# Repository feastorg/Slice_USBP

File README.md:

<div align="center">
  <!-- Title: -->
  
  <h2><a href="https://github.com/uwo-fast/Slice_TEMP"> STEP Slice </a></h2>
  <!-- Labels: -->
  <!-- First row: -->

  <a href="https://certification.oshwa.org/">
    
    <!-- img src="https://img.shields.io/badge/OSHWA-Certified-darkgreen?style=flat-square" height="20" alt="OSHWA" -->       <!-- img src="https://img.shields.io/badge/OSHWA-Pending-darkorange?style=flat-square" height="20" alt="OSHWA" -->
  </a>

  <!-- Second row: -->
  <br>

  <!-- Short description: -->
  <h3>Universal Serial Bus (USB) Port Slice for BREAD.</h3>
</div>

## Introduction
[Provide a brief introduction to the project, including the motivation and goals. Explain the significance and context of the research.]

## Project Overview
[Describe the project in more detail. This section can be split into subsections if necessary.]

## Installation
[Provide instructions for installing any necessary software or hardware components.]

## Usage
[Explain how to use the project. Include examples and screenshots if applicable.]

### Basic Usage
[Provide basic usage instructions.]

### Advanced Usage
[Provide advanced usage instructions, including any optional features or configurations.]

## Documentation
[Link to the detailed documentation if available. Provide instructions on how to access and navigate the documentation.]

## Contributing
[Explain how others can contribute to the project. Include guidelines for submitting issues, pull requests, and any coding standards.]

### Code of Conduct
[Link to the project's code of conduct if available.]

## License
[State the license under which the project is distributed. Include a link to the full license text.]

## Acknowledgements
[Acknowledge any contributors, collaborators, funding sources, or organizations that supported the project.]

## Contact
[Provide contact information for the project maintainer(s) or lead researcher(s). Include an email address or a link to a contact form.]

---

<div align="center">
  
</div>

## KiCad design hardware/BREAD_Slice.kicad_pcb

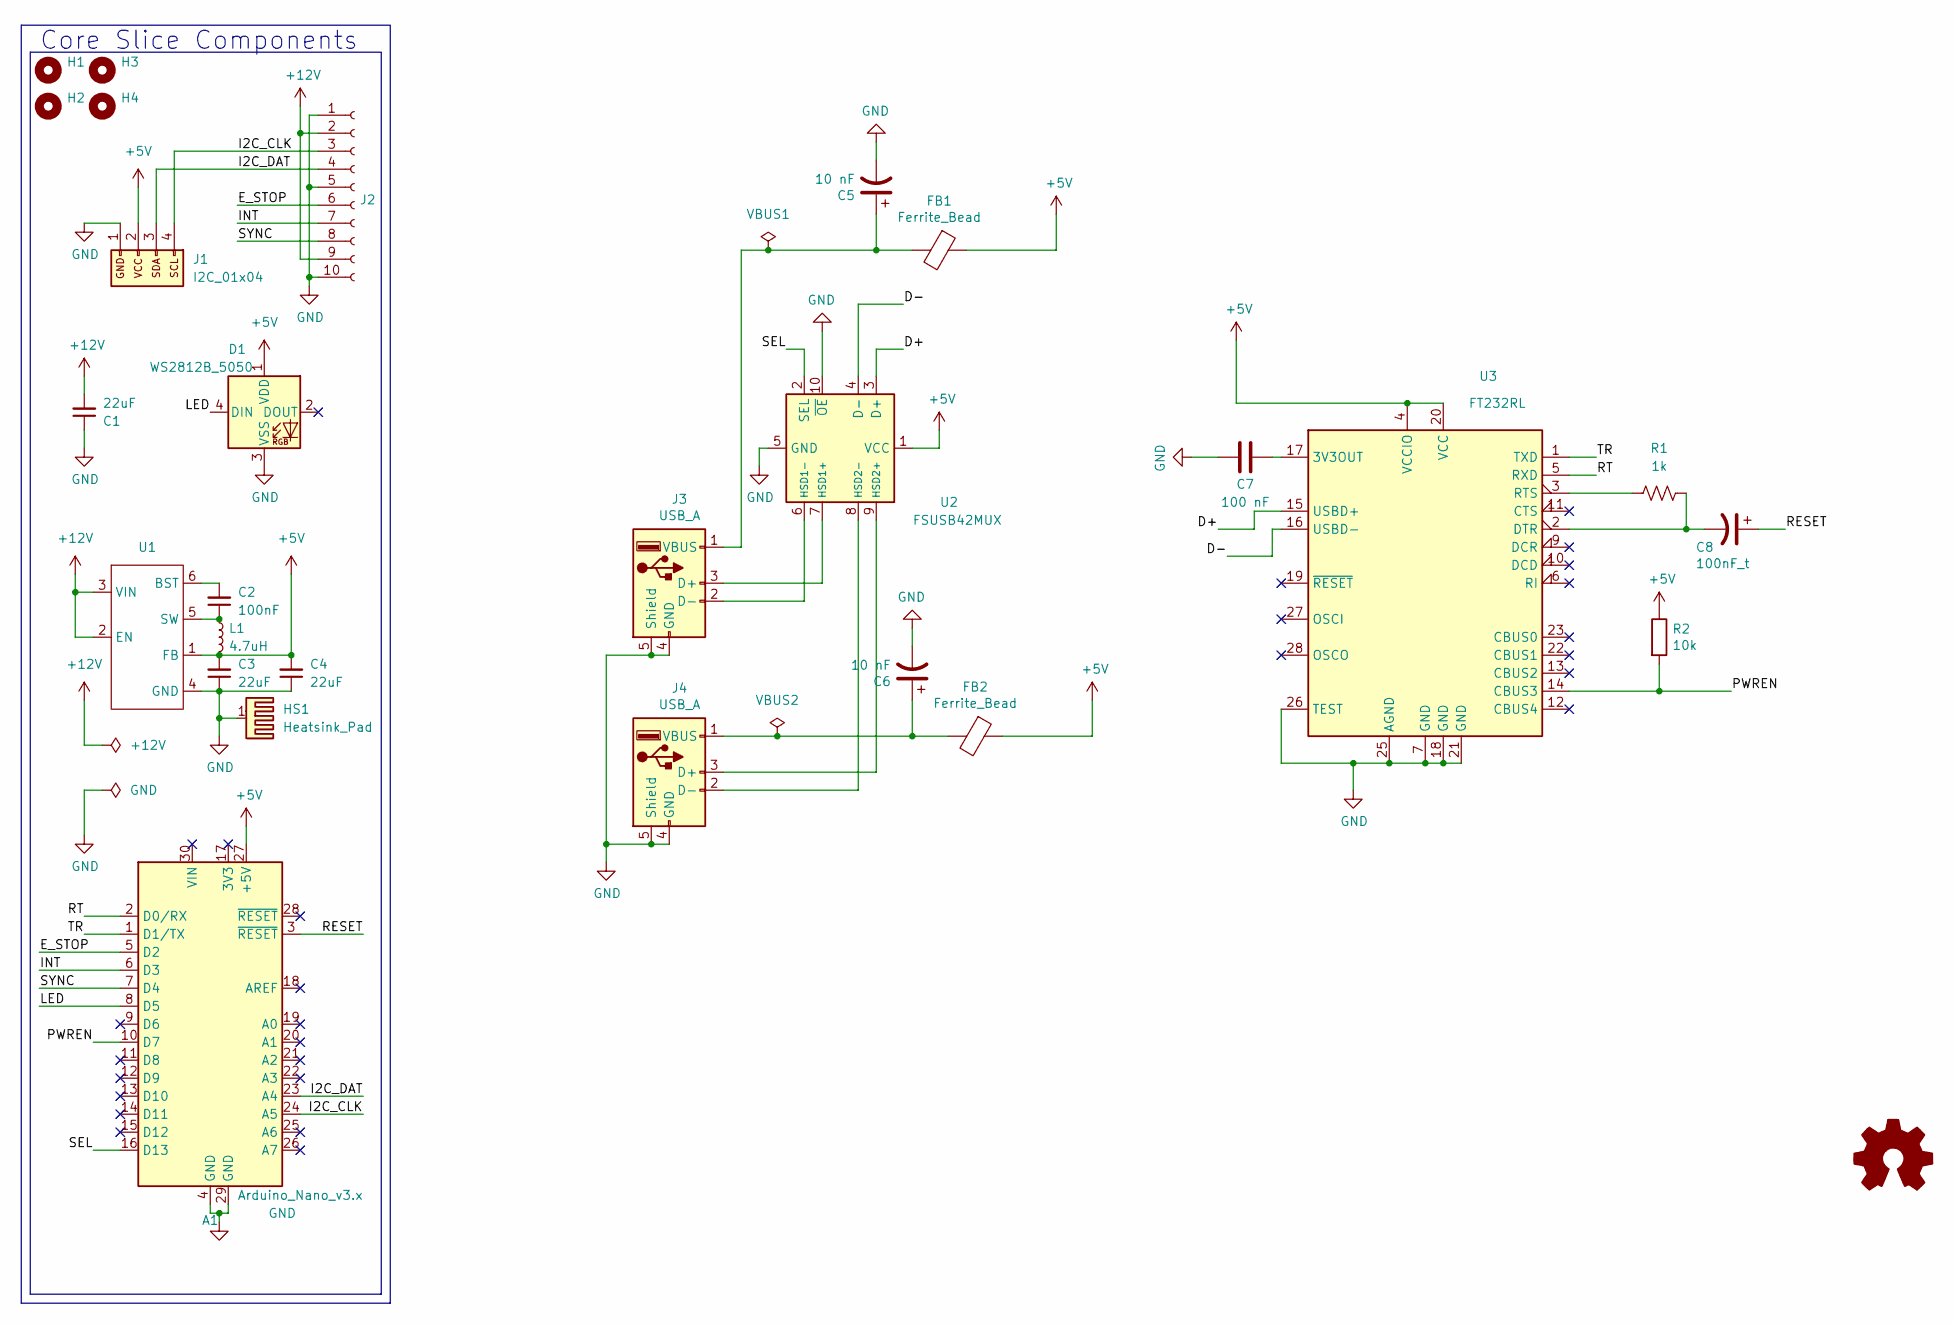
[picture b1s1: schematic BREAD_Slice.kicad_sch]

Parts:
A1: Arduino_Nano_v3.x; Arduino_Nano
C1, C3, C4: 22uF; C_1206_3216Metric_Pad1.33x1.80mm_HandSolder
C2: 100nF; C_1206_3216Metric_Pad1.33x1.80mm_HandSolder
C5, C6: 10 nF; C_1206_3216Metric_Pad1.33x1.80mm_HandSolder; Part # T491C106K025AT
C7: 100 nF; C_1206_3216Metric_Pad1.33x1.80mm_HandSolder
C8: 100nF_t; C_1206_3216Metric_Pad1.33x1.80mm_HandSolder; Part # T491C106K025AT
D1: WS2812B_5050; WS2812-5050-4PIN
FB1, FB2: Ferrite_Bead; R_1206_3216Metric_Pad1.30x1.75mm_HandSolder
H1, H2, H3, H4: MountingHole; MountingHole_5mm
HS1: Heatsink_Pad; Thermal_Pad
J1: I2C_01x04; JST_SH_SM04B-SRSS-TB_1x04-1MP_P1.00mm_Horizontal
J2: Conn_01x10_Female; PinSocket_1x10_P2.54mm_Horizontal
J3, J4: USB_A; USB_A_Molex_67643_Horizontal
L1: 4.7uH; L_1210_3225Metric
R1: 1k; R_1206_3216Metric_Pad1.30x1.75mm_HandSolder
R2: 10k; R_1206_3216Metric_Pad1.30x1.75mm_HandSolder
U1: TSOT-23-6
U2: FSUSB42MUX; MSOP-10_3x3mm_P0.5mm
U3: FT232RL; SSOP-28_5.3x10.2mm_P0.65mm

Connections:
+5V: A1.27 (+5V), C3.2, C4.2, D1.1 (VDD), FB1.1, FB2.1, J1.2, L1.2, R2.1, U1.1 (FB), U2.1 (VCC), U3.4 (VCCIO), U3.20 (VCC)
+12V: C1.2, J2.2, J2.9, U1.2 (EN), U1.3 (VIN)
/D+: U2.3 (D+), U3.15 (USBD+)
/D-: U2.4 (D-), U3.16 (USBD-)
/E_STOP: A1.5 (D2), J2.6
/I2C_CLK: A1.24 (A5), J1.4, J2.3
/I2C_DAT: A1.23 (A4), J1.3, J2.4
/INT: A1.6 (D3), J2.7
/LED: A1.8 (D5), D1.4 (DIN)
/PWREN: A1.10 (D7), R2.2, U3.14 (CBUS3)
/RESET: A1.3 (~RESET), C8.1
/RT: A1.2 (D0/RX), U3.5 (RXD)
/SEL: A1.16 (D13), U2.2 (SEL)
/SYNC: A1.7 (D4), J2.8
/TR: A1.1 (D1/TX), U3.1 (TXD)
GND: A1.4 (GND), A1.29 (GND), C1.1, C3.1, C4.1, C5.2, C6.2, C7.1, D1.3 (VSS), HS1.1, J1.1, J2.1, J2.5, J2.10, J3.4 (GND), J3.5 (Shield), J4.4 (GND), J4.5 (Shield), U1.4 (GND), U2.5 (GND), U2.10 (~OE), U3.7 (GND), U3.18 (GND), U3.21 (GND), U3.25 (AGND), U3.26 (TEST)
unnamed: J3.3 (D+), U2.7 (HSD1+)
unnamed: J3.2 (D-), U2.6 (HSD1-)
unnamed: C5.1, FB1.2, J3.1 (VBUS)
unnamed: J4.3 (D+), U2.9 (HSD2+)
unnamed: J4.2 (D-), U2.8 (HSD2-)
unnamed: C6.1, FB2.2, J4.1 (VBUS)
unnamed: C2.2, U1.6 (BST)
unnamed: C2.1, L1.1, U1.5 (SW)
unnamed: C7.2, U3.17 (3V3OUT)
unnamed: C8.2, R1.2, U3.2 (DTR)
unnamed: R1.1, U3.3 (RTS)

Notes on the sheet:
Core Slice Components

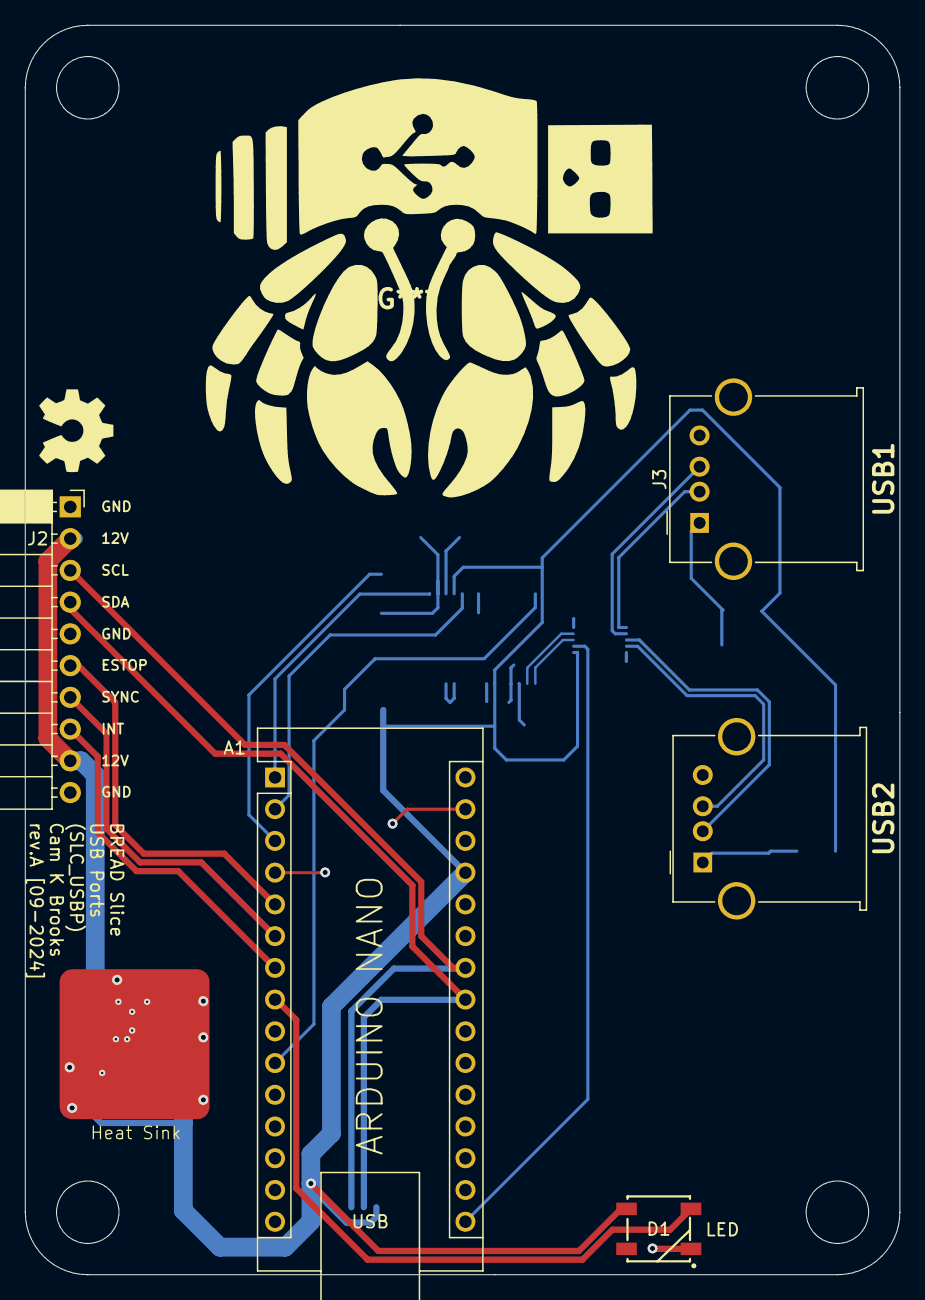
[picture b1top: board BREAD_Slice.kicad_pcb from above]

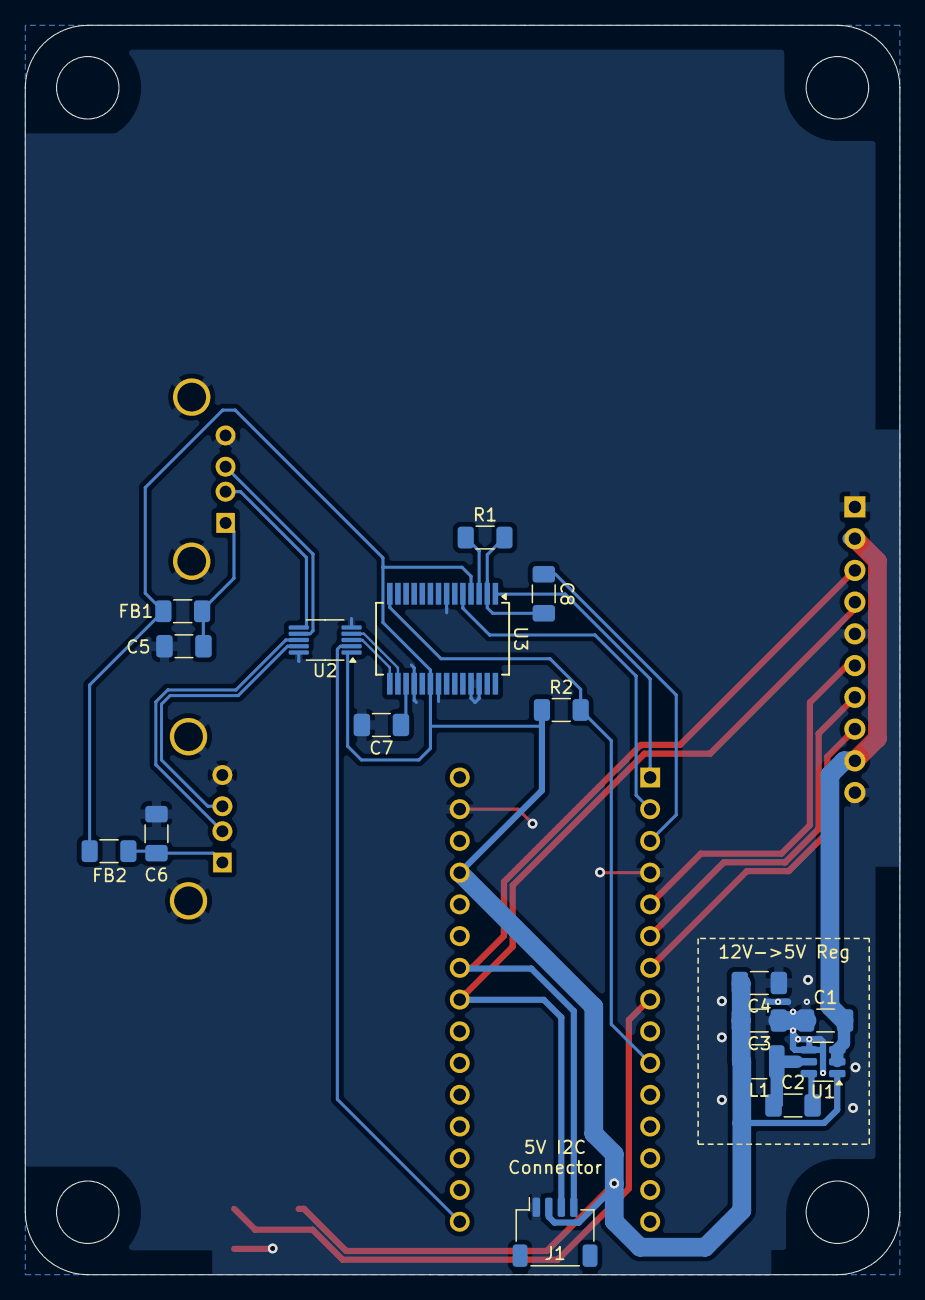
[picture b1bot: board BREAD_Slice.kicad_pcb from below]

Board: 2 copper layers, 70.0 x 100.0 mm, 28 parts (17 on the bottom side), 27 nets.

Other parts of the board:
Logo1: Logo_Open_Hardware_Small; OSHW-Symbol_6.7x6mm_SilkScreen

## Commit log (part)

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2024-09-10 optimized pcb and updated to new core
2024-09-30 JLCPCB order rev-A
2026-05-20 Add slice.yaml manifest (schema v1.0)
2026-05-24 Add KiBot/docs pipeline
2026-05-24 📄 KiBot index + board renders (auto)
2026-05-24 Update TODO with CI results
2026-05-24 Standardize TODO.md with Pass 1/Pass 2 structure
